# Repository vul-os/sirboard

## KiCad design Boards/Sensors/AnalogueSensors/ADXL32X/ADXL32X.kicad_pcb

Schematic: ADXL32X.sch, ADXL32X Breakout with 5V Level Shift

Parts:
C1, C2: 10uF; C_0805_2012Metric; Part C95841
C3, C4, C5: 100nF; C_0603_1608Metric; Part C42998
H1, H2, H3, H4: MountingHole; MountingHole_M2.5_SirBoard
J1, J2: Conn_01x04; PinHeader_1x04_P2.54mm_Vertical
U1: AP2127K-3.3; SOT-23-5; Part C156285
U2: ADXL32X; QFN-16-1EP_4x4mm_P0.65mm_EP2.1x2.1mm; Part C208133; C207396; 759-1998; 709-0136; 7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

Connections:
3V3: C2.1, J1.2, U1.5, U2.14 (VS), U2.15 (VS)
5V: C1.1, J1.1, U1.1, U1.3
GND: C1.2, C2.2, C3.2, C4.2, C5.2, J1.3, J2.1, U1.2, U2.3 (COM), U2.5 (COM), U2.6 (COM), U2.7 (COM)
ST: J1.4, U2.2 (ST)
XO: C4.1, J2.2, U2.12 (XOUT)
YO: C5.1, J2.3, U2.10 (YOUT)
ZO: C3.1, J2.4, U2.8 (ZOUT)

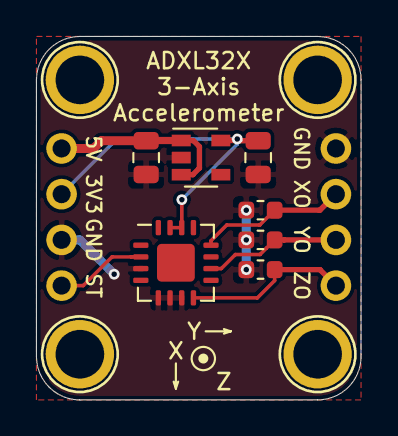
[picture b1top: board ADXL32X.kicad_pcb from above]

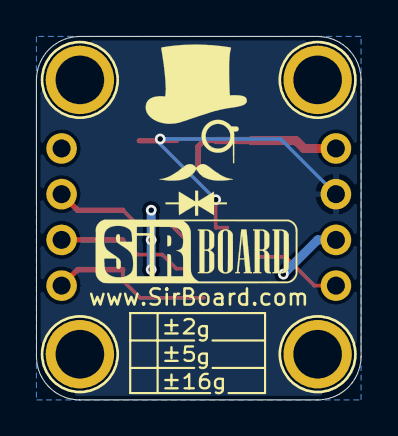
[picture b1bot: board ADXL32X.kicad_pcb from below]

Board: 2 copper layers, 18.0 x 20.2 mm, 13 parts (2 on the bottom side), 7 nets.

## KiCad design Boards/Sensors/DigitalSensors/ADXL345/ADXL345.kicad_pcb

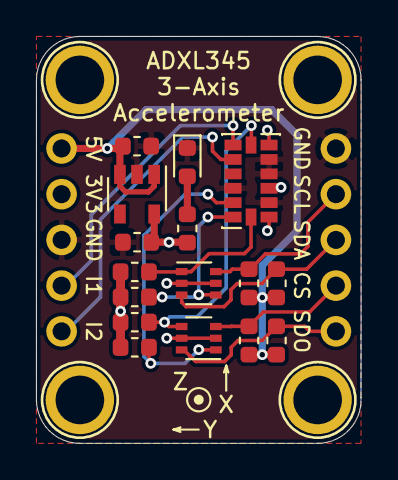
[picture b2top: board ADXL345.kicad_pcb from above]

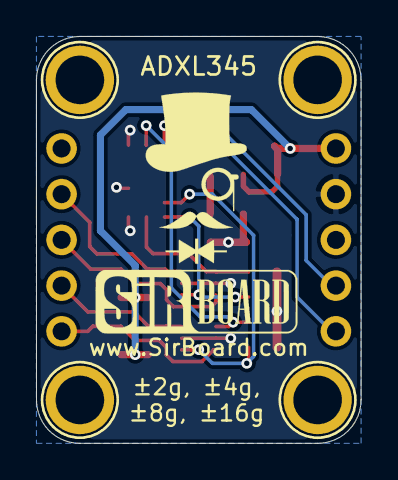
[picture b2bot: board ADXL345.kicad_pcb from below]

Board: 2 copper layers, 18.0 x 22.6 mm, 22 parts (2 on the bottom side), 14 nets.

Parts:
C1, C2: 1uF; C_0603_1608Metric
D1: LED; LED_0603_1608Metric
H1, H2, H3, H4: MountingHole; MountingHole_M2.5_SirBoard
J1, J2: Conn_01x05; PinHeader_1x05_P2.54mm_Vertical
Q1, Q2: BSS138DW; SOT-363_SC-70-6
R1, R2, R3, R4, R5, R7, R8, R9: 10K; R_0603_1608Metric
R6: 1K; R_0603_1608Metric
U1: AP2127K-3.3; SOT-23-5
U2: ADXL345; LGA-14_3x5mm_P0.8mm_LayoutBorder1x6y

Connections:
3V3: C2.1, J1.2, Q1.2, Q1.5, Q2.2, Q2.5, R1.2, R3.2, R5.2, R6.1, R8.2, U1.5, U2.1, U2.3, U2.6
5V: C1.1, J1.1, R2.1, R4.1, R7.1, R9.1, U1.1, U1.3
CSB_3V3: Q2.4, R8.1, U2.7
CSB_5V: J2.4, Q2.3, R9.2
GND: C1.2, C2.2, D1.1, J1.3, J2.1, U1.2, U2.2, U2.4, U2.5, U2.11
INT1: J1.4, U2.8
INT2: J1.5, U2.9
unnamed: D1.2, R6.2
SCK_3V3: Q1.1, R1.1, U2.14
SCK_5V: J2.2, Q1.6, R2.2
SDI_3V3: Q1.4, R3.1, U2.13
SDI_5V: J2.3, Q1.3, R4.2
SDO_3V3: Q2.1, R5.1, U2.12
SDO_5V: J2.5, Q2.6, R7.2

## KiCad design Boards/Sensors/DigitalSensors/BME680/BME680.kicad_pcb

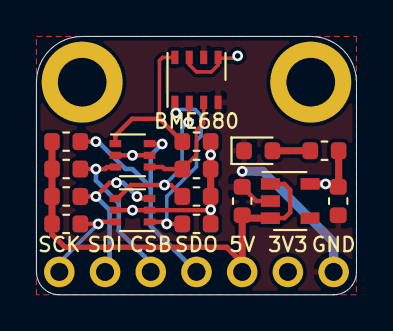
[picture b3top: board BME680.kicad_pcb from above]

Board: 2 copper layers, 17.8 x 14.4 mm, 19 parts (1 on the bottom side), 12 nets.

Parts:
BME680: BME680; Bosch_LGA-8_3x3mm_P0.8mm_ClockwisePinNumbering
C1, C2: 1uF; C_0603_1608Metric
D1: LED; LED_0603_1608Metric
H3, H4: MountingHole; MountingHole_2.7mm_M2.5_ISO14580_Pad
J1: Conn_01x07; PinHeader_1x07_P2.54mm_Vertical
Q1, Q2: BSS138DW; SOT-363_SC-70-6
R1, R2, R3, R4, R5, R7, R8, R9: 10K; R_0603_1608Metric
R6: 1K; R_0603_1608Metric
U1: AP2127K-3.3; SOT-23-5

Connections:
3V3: BME680.6, BME680.8, C2.1, J1.6, Q1.2, Q1.5, Q2.2, Q2.5, R1.2, R3.2, R5.2, R6.1, R8.2, U1.5
5V: C1.1, J1.5, R2.1, R4.1, R7.1, R9.1, U1.1, U1.3
CSB_3V3: BME680.2, Q2.4, R8.1
CSB_5V: J1.3, Q2.3, R9.2
GND: BME680.1, BME680.7, C1.2, C2.2, D1.1, J1.7, U1.2
unnamed: D1.2, R6.2
SCK_3V3: BME680.4, Q1.1, R1.1
SCK_5V: J1.1, Q1.6, R2.2
SDI_3V3: BME680.3, Q1.4, R3.1
SDI_5V: J1.2, Q1.3, R4.2
SDO_3V3: BME680.5, Q2.1, R5.1
SDO_5V: J1.4, Q2.6, R7.2

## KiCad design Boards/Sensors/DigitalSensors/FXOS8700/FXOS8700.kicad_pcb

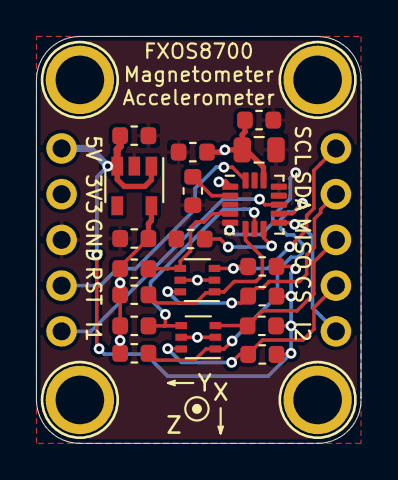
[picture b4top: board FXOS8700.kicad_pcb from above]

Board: 2 copper layers, 18.0 x 22.6 mm, 25 parts (0 on the bottom side), 16 nets.

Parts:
C1, C3: 1uF; C_0603_1608Metric
C2, C4, C6, C7: 100nF; C_0603_1608Metric
C5: 4.7uF; C_0805_2012Metric
H1, H2, H3, H4: MountingHole; MountingHole_M2.5_SirBoard
J1, J2: Conn_01x05; PinHeader_1x05_P2.54mm_Vertical
Q1, Q2: BSS138DW; SOT-363_SC-70-6
R1, R2, R3, R4, R5, R6, R7, R8: 10K; R_0603_1608Metric
U1: AP2127K-3.3; SOT-23-5
U2: FXOS8700; QFN-COL-16-P=0.5

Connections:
3V3: C2.1, C3.1, C5.1, C7.1, J1.2, Q1.2, Q1.5, Q2.2, Q2.5, R1.2, R3.2, R5.2, R7.2, U1.5, U2.1, U2.14
5V: C1.1, J1.1, R2.1, R4.1, R6.1, R8.1, U1.1, U1.3
CS_3V3: Q1.1, R1.1, U2.10
CS_5V: J2.4, Q1.6, R2.2
GND: C1.2, C2.2, C3.2, C4.2, C5.2, C6.2, C7.2, J1.3, U1.2, U2.3, U2.5, U2.12, U2.13
INT1: J1.5, U2.11
INT2: J2.5, U2.9
MISO_3V3: Q1.4, R3.1, U2.7
MISO_5V: J2.3, Q1.3, R4.2
unnamed: C4.1, U2.2
unnamed: C6.1, U2.8
RST: J1.4, U2.16
SCL_3V3: Q2.4, R7.1, U2.4
SCL_5V: J2.1, Q2.3, R8.2
SDA_3V3: Q2.1, R5.1, U2.6
SDA_5V: J2.2, Q2.6, R6.2

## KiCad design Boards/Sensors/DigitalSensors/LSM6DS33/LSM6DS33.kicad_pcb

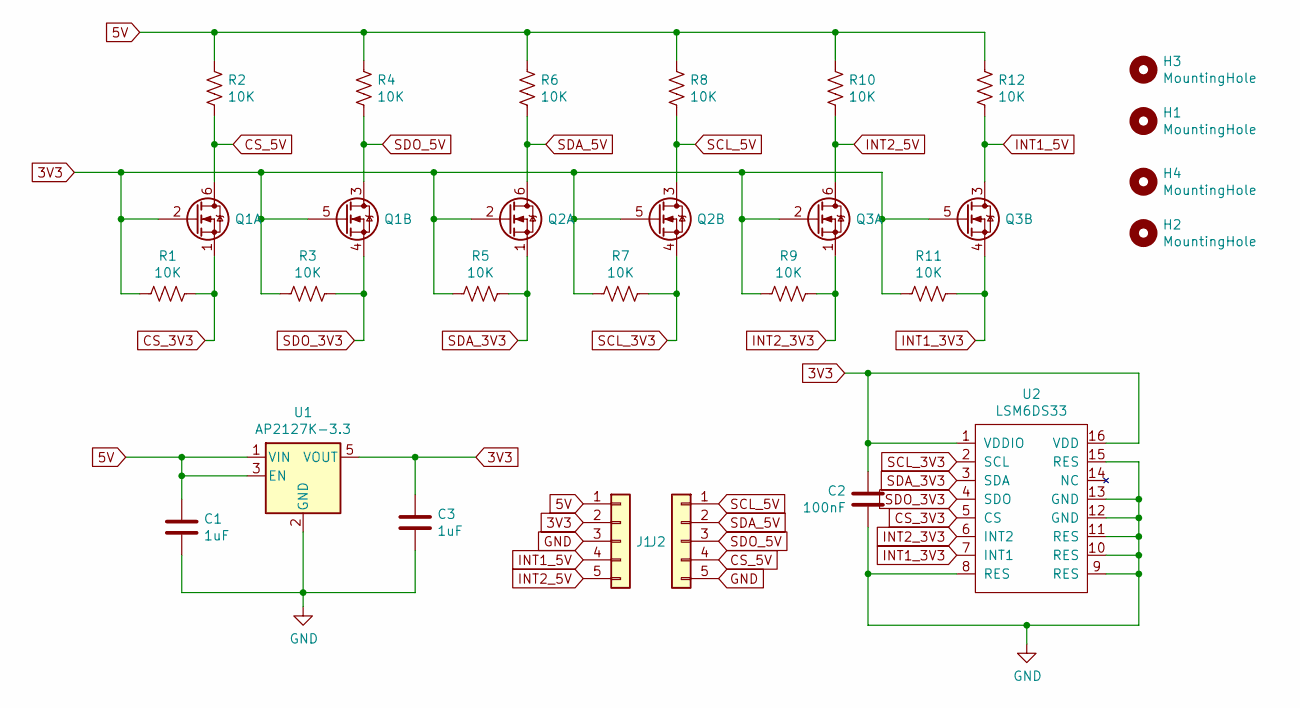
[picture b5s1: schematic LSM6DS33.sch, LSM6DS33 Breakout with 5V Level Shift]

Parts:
C1, C3: 1uF; C_0603_1608Metric; Part C29936
C2: 100nF; C_0603_1608Metric; Part C42998
H1, H2, H3, H4: MountingHole; MountingHole_M2.5_SirBoard
J1, J2: Conn_01x05; PinHeader_1x05_P2.54mm_Vertical
Q1, Q2, Q3: BSS138DW; SOT-363_SC-70-6
R1, R2, R3, R4, R5, R6, R7, R8, R9, R10, R11, R12: 10K; R_0603_1608Metric; Part C99198
U1: AP2127K-3.3; SOT-23-5; Part C156285
U2: LSM6DS33; QFN-COL-16-P=0.5; Part C95231

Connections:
3V3: C2.1, C3.1, J1.2, Q1.2 (G), Q1.5 (G), Q2.2 (G), Q2.5 (G), Q3.2 (G), Q3.5 (G), R1.2, R3.2, R5.2, R7.2, R9.2, R11.2, U1.5 (VOUT), U2.1 (VDDIO), U2.16 (VDD)
5V: C1.1, J1.1, R2.1, R4.1, R6.1, R8.1, R10.1, R12.1, U1.1 (VIN), U1.3 (EN)
CS_3V3: Q1.1 (S), R1.1, U2.5 (CS)
CS_5V: J2.4, Q1.6 (D), R2.2
GND: C1.2, C2.2, C3.2, J1.3, J2.5, U1.2 (GND), U2.8 (RES), U2.9 (RES), U2.10 (RES), U2.11 (RES), U2.12 (GND), U2.13 (GND), U2.15 (RES)
INT1_3V3: Q3.4 (S), R11.1, U2.7 (INT1)
INT1_5V: J1.4, Q3.3 (D), R12.2
INT2_3V3: Q3.1 (S), R9.1, U2.6 (INT2)
INT2_5V: J1.5, Q3.6 (D), R10.2
SCL_3V3: Q2.4 (S), R7.1, U2.2 (SCL)
SCL_5V: J2.1, Q2.3 (D), R8.2
SDA_3V3: Q2.1 (S), R5.1, U2.3 (SDA)
SDA_5V: J2.2, Q2.6 (D), R6.2
SDO_3V3: Q1.4 (S), R3.1, U2.4 (SDO)
SDO_5V: J2.3, Q1.3 (D), R4.2

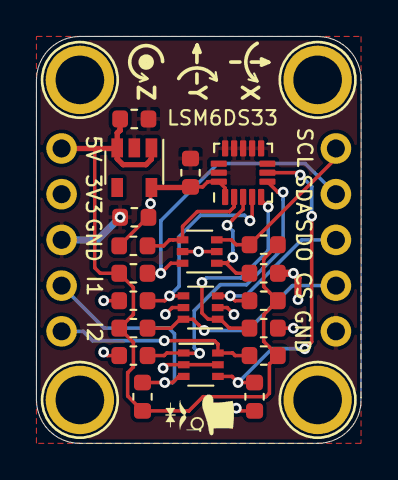
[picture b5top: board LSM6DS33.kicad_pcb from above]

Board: 2 copper layers, 18.0 x 22.6 mm, 26 parts (0 on the bottom side), 15 nets.

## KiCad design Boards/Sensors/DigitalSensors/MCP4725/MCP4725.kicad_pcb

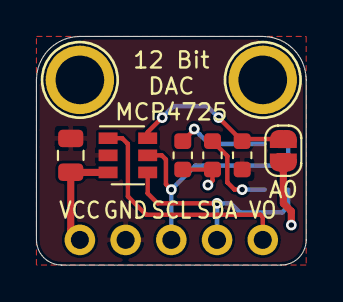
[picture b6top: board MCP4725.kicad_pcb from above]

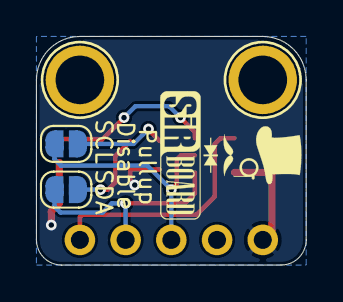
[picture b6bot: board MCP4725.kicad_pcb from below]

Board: 2 copper layers, 15.0 x 12.7 mm, 11 parts (2 on the bottom side), 8 nets.

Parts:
A0: SolderJumper_2_Open; SolderJumper-2_P1.3mm_Open_RoundedPad1.0x1.5mm
C1: 10uF; C_0805_2012Metric
H1, H2: MountingHole; MountingHole_M2.5_SirBoard
J1: Conn_01x05; PinHeader_1x05_P2.54mm_Vertical
MCP4725: MCP4725; SOT-23-6
R1, R2, R3: 10K; R_0603_1608Metric
SCL: SolderJumper_2_Open; SolderJumper-2_P1.3mm_Open_RoundedPad1.0x1.5mm
SDA: SolderJumper_2_Open; SolderJumper-2_P1.3mm_Open_RoundedPad1.0x1.5mm

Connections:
/A0: A0.2, MCP4725.6, R1.1
GND: C1.2, J1.2, MCP4725.2, R1.2
unnamed: R2.2, SCL.1
unnamed: R3.2, SDA.1
SCL: J1.3, MCP4725.5, SCL.2
SDA: J1.4, MCP4725.4, SDA.2
VCC: A0.1, C1.1, J1.1, MCP4725.3, R2.1, R3.1
VOUT: J1.5, MCP4725.1

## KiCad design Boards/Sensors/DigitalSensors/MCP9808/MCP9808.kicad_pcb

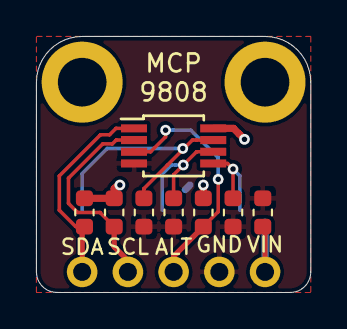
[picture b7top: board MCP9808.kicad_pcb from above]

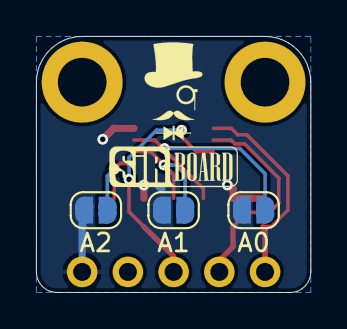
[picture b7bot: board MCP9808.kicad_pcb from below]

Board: 2 copper layers, 15.2 x 14.2 mm, 14 parts (4 on the bottom side), 8 nets.

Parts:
A0, A1, A2: SolderJumper_2_Open; SolderJumper-2_P1.3mm_Open_RoundedPad1.0x1.5mm
C1: 1uF; C_0603_1608Metric
H1, H2: MountingHole; MountingHole_2.7mm_M2.5_ISO14580_Pad
J1: Conn_01x05; PinHeader_1x05_P2.54mm_Vertical
MCP: MCP9808; MSOP-8_3x3mm_P0.65mm
R1, R2, R6: 4K7; R_0603_1608Metric
R3, R4, R5: 10K; R_0603_1608Metric

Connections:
A0: A0.1, MCP.7, R3.1
A1: A1.1, MCP.6, R4.1
A2: A2.1, MCP.5, R5.1
ALERT: J1.3, MCP.3, R2.2
GND: C1.2, J1.4, MCP.4, R3.2, R4.2, R5.2
SCL: J1.2, MCP.2, R1.2
SDA: J1.1, MCP.1, R6.2
VIN: A0.2, A1.2, A2.2, C1.1, J1.5, MCP.8, R1.1, R2.1, R6.1
